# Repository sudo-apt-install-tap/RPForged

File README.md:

## RPFORGED
This is a custom development board based on the RP 2040 Chip. It has 29 GPIO headers. It has 16MiB Flash storage. It is great for those who want minimalism with style.

## Design Decisions

This project was built to be a minimal but flexible RP2040 devboard
that I could understand end-to-end.

- **RP2040** was chosen for its strong ecosystem, PIO support,and availability.
- **USB-C** was used for durability and modern compatibility.
- The board exposes commonly used GPIOs to make it suitable for keyboards, HID projects, and general prototyping.
- The design avoids unnecessary peripherals to keep cost,complexity, and assembly time low.

## What Can This Board Be Used For?

- Custom keyboards and macropads
- RP2040 experimentation and learning
- USB HID projects
- General embedded prototyping

## Images ( RENDERS )

## BOM

PCB + PCBA = $58
Miscellaneous Costs = $2

## Manufacturing Plan

For this project, only **2 boards will be assembled through JLCPCB**
to validate the design and ensure reliability.

Any additional boards will be assembled by hand using a hotplate once I have access to one. This allows me to learn hands-on SMD assembly while keeping costs low and avoiding unnecessary PCBA orders.

## Build Images and Videos

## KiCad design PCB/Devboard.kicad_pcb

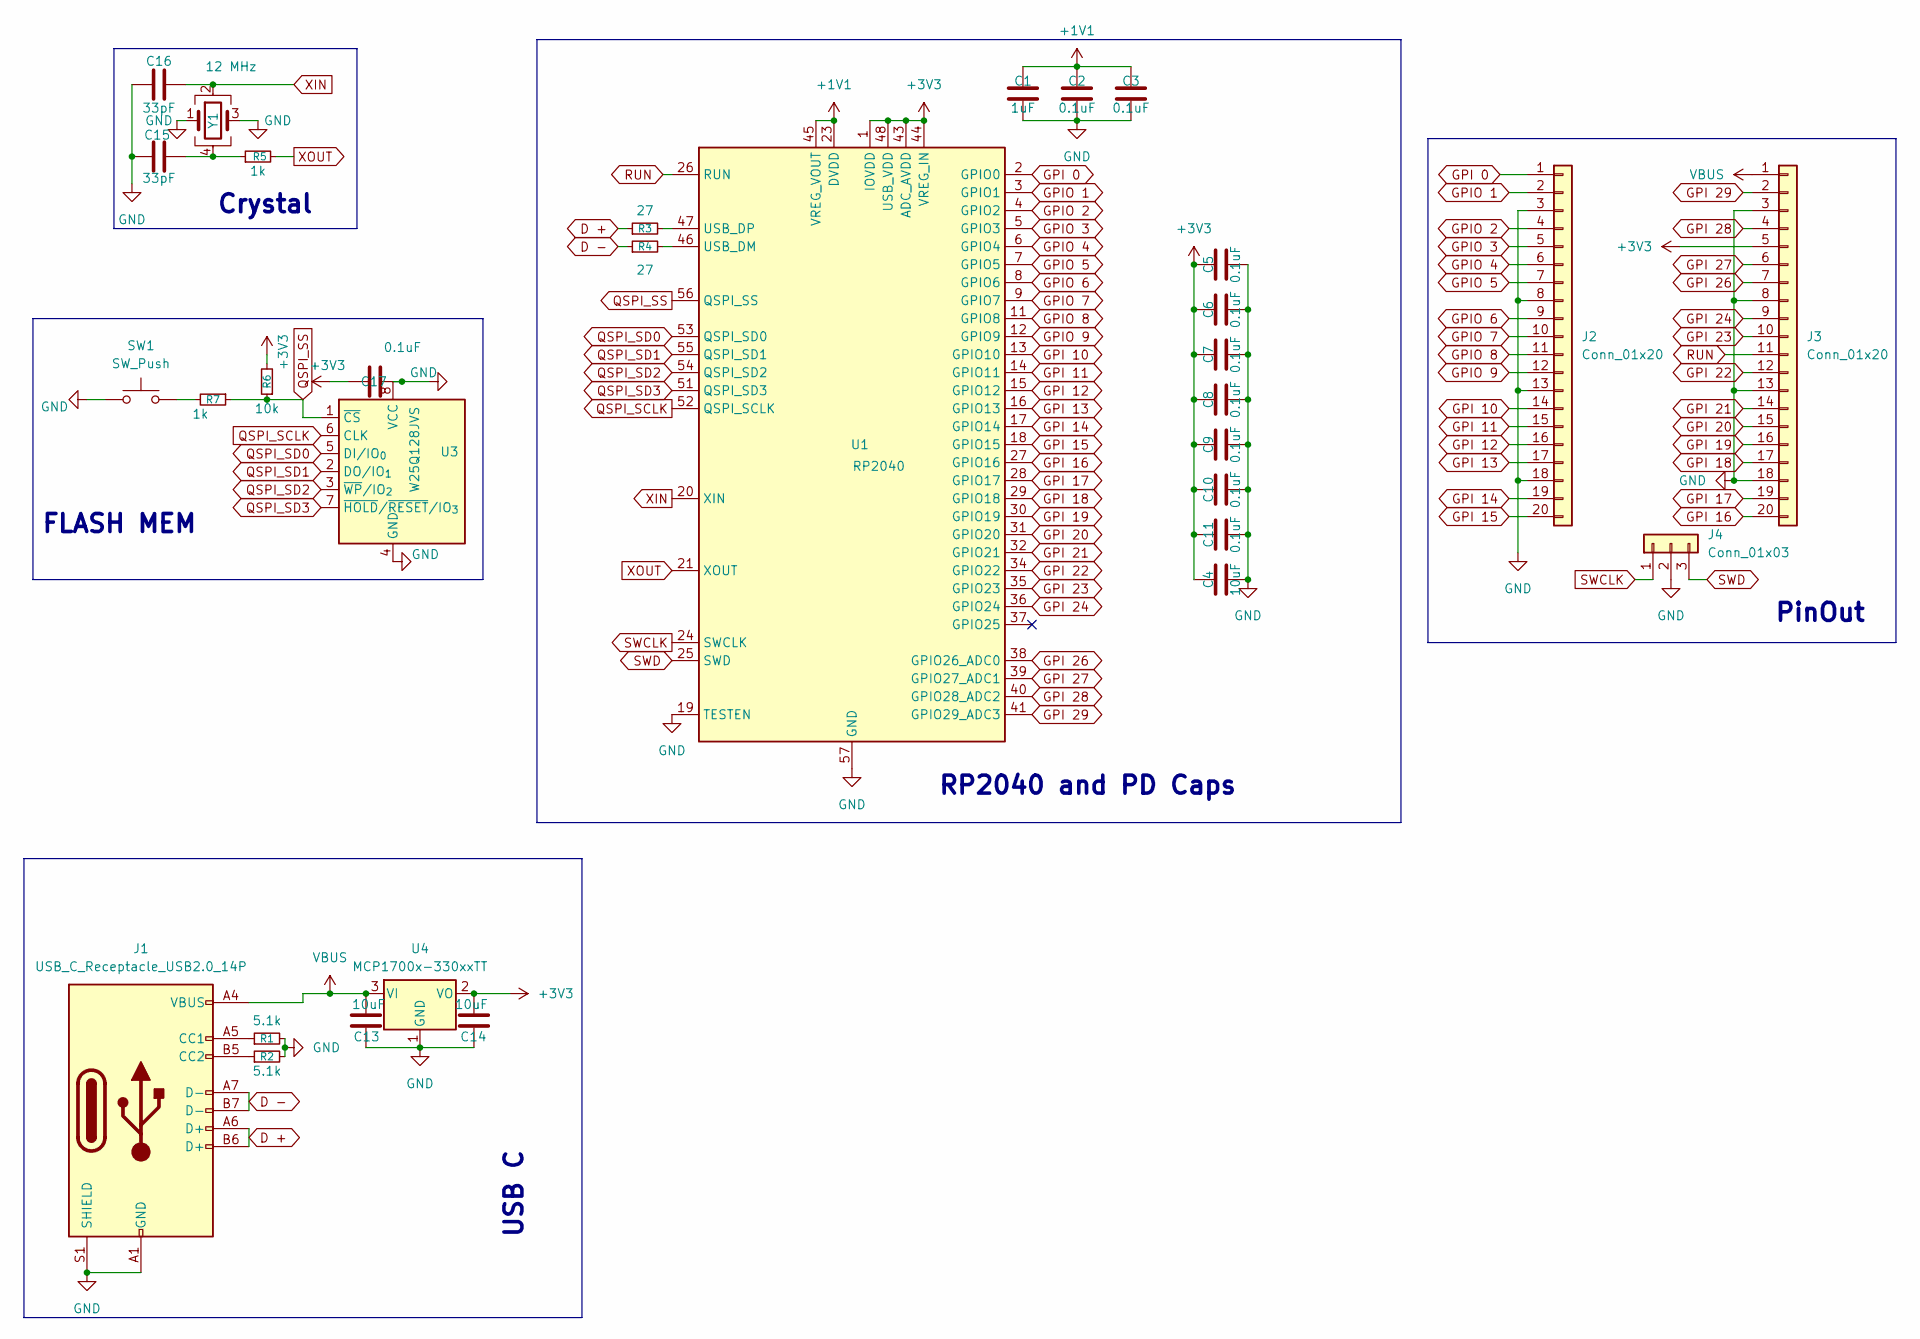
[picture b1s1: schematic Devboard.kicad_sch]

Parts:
C1: 1uF; C_0402_1005Metric
C2, C3, C5, C6, C7, C8, C9, C10, C11, C17: 0.1uF; C_0402_1005Metric
C4: 10uF; C_0402_1005Metric
C13, C14: 10uF; C_0201_0603Metric
C15, C16: 33pF; C_0402_1005Metric
J1: USB_C_Receptacle_USB2.0_14P; USB_C_Receptacle_HRO_TYPE-C-31-M-12
J2, J3: Conn_01x20; PinHeader_1x20_P2.54mm_Vertical
J4: Conn_01x03; PinHeader_1x03_P2.54mm_Vertical
R1, R2: 5.1k; R_0402_1005Metric
R3, R4: 27; R_0402_1005Metric
R5, R7: 1k; R_0402_1005Metric
R6: 10k; R_0402_1005Metric
SW1: SW_Push; SW_Push_SPST_NO_Alps_SKRK
U1: RP2040; QFN-56-1EP_7x7mm_P0.4mm_EP3.2x3.2mm
U3: W25Q128JVS; Winbond_USON-8-1EP_3x2mm_P0.5mm_EP0.2x1.6mm
U4: MCP1700x-330xxTT; SOT-23
Y1: 12 MHz; Crystal_SMD_3225-4Pin_3.2x2.5mm

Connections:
+1V1: C1.1, C2.1, C3.1, U1.23 (DVDD), U1.45 (VREG_VOUT), U1.50 (DVDD)
+3V3: C4.1, C5.1, C6.1, C7.1, C8.1, C9.1, C10.1, C11.1, C14.2, C17.1, J3.5, R6.2, U1.1 (IOVDD), U1.10 (IOVDD), U1.22 (IOVDD), U1.33 (IOVDD), U1.42 (IOVDD), U1.43 (ADC_AVDD), U1.44 (VREG_IN), U1.48 (USB_VDD), U1.49 (IOVDD), U4.2 (VO)
D +: J1.A6 (D+), J1.B6 (D+), R3.1
D -: J1.A7 (D-), J1.B7 (D-), R4.1
GND: C1.2, C2.2, C3.2, C4.2, C5.2, C6.2, C7.2, C8.2, C9.2, C10.2, C11.2, C13.1, C14.1, C15.2, C16.2, C17.2, J1.A1 (GND), J1.A12 (GND), J1.B1 (GND), J1.B12 (GND), J1.S1 (SHIELD), J2.3, J2.8, J2.13, J2.18, J3.3, J3.8, J3.13, J3.18, J4.2, R1.2, R2.2, SW1.1, U1.19 (TESTEN), U1.57 (GND), U3.4 (GND), U3.8 (VCC), U4.1 (GND), Y1.1, Y1.3
GPI 0: J2.1, U1.2 (GPIO0)
GPI 10: J2.14, U1.13 (GPIO10)
GPI 11: J2.15, U1.14 (GPIO11)
GPI 12: J2.16, U1.15 (GPIO12)
GPI 13: J2.17, U1.16 (GPIO13)
GPI 14: J2.19, U1.17 (GPIO14)
GPI 15: J2.20, U1.18 (GPIO15)
GPI 16: J3.20, U1.27 (GPIO16)
GPI 17: J3.19, U1.28 (GPIO17)
GPI 18: J3.17, U1.29 (GPIO18)
GPI 19: J3.16, U1.30 (GPIO19)
GPI 20: J3.15, U1.31 (GPIO20)
GPI 21: J3.14, U1.32 (GPIO21)
GPI 22: J3.12, U1.34 (GPIO22)
GPI 23: J3.10, U1.35 (GPIO23)
GPI 24: J3.9, U1.36 (GPIO24)
GPI 26: J3.7, U1.38 (GPIO26_ADC0)
GPI 27: J3.6, U1.39 (GPIO27_ADC1)
GPI 28: J3.4, U1.40 (GPIO28_ADC2)
GPI 29: J3.2, U1.41 (GPIO29_ADC3)
GPIO 1: J2.2, U1.3 (GPIO1)
GPIO 2: J2.4, U1.4 (GPIO2)
GPIO 3: J2.5, U1.5 (GPIO3)
GPIO 4: J2.6, U1.6 (GPIO4)
GPIO 5: J2.7, U1.7 (GPIO5)
GPIO 6: J2.9, U1.8 (GPIO6)
GPIO 7: J2.10, U1.9 (GPIO7)
GPIO 8: J2.11, U1.11 (GPIO8)
GPIO 9: J2.12, U1.12 (GPIO9)
unnamed: C15.1, R5.1, Y1.4
unnamed: J1.A5 (CC1), R1.1
unnamed: J1.B5 (CC2), R2.1
unnamed: R7.2, SW1.2
unnamed: R4.2, U1.46 (USB_DM)
unnamed: R3.2, U1.47 (USB_DP)
QSPI_SCLK: U1.52 (QSPI_SCLK), U3.6 (CLK)
QSPI_SD0: U1.53 (QSPI_SD0), U3.5 (DI/IO_{0})
QSPI_SD1: U1.55 (QSPI_SD1), U3.2 (DO/IO_{1})
QSPI_SD2: U1.54 (QSPI_SD2), U3.3 (~WP/IO_{2})
QSPI_SD3: U1.51 (QSPI_SD3), U3.7 (~HOLD/~RESET/IO_{3})
QSPI_SS: R6.1, R7.1, U1.56 (QSPI_SS), U3.1 (~CS)
RUN: J3.11, U1.26 (RUN)
SWCLK: J4.1, U1.24 (SWCLK)
SWD: J4.3, U1.25 (SWD)
VBUS: C13.2, J1.A4 (VBUS), J1.A9 (VBUS), J1.B4 (VBUS), J1.B9 (VBUS), J3.1, U4.3 (VI)
XIN: C16.1, U1.20 (XIN), Y1.2
XOUT: R5.2, U1.21 (XOUT)

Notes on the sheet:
USB C
PinOut
FLASH MEM
RP2040 and PD Caps
Crystal

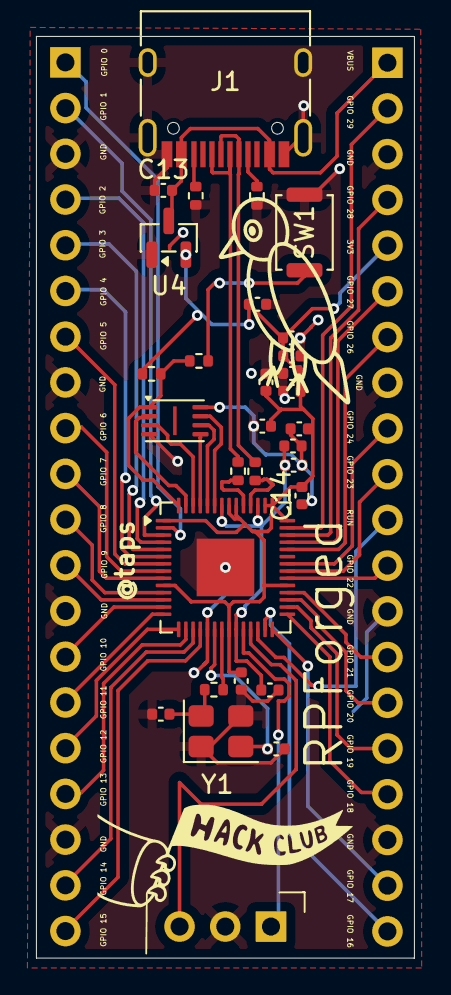
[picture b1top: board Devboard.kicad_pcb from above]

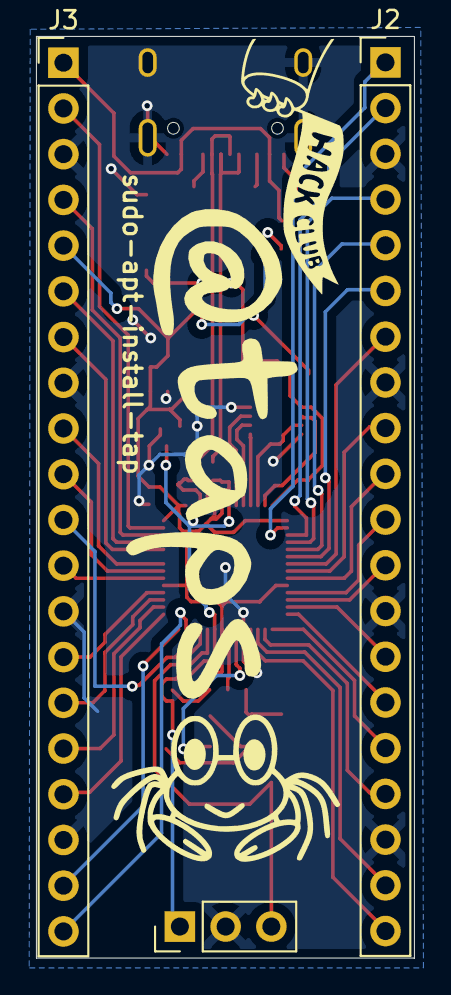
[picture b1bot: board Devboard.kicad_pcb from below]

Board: 2 copper layers, 21.0 x 51.2 mm, 32 parts (3 on the bottom side), 52 nets.

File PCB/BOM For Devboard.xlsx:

Id | Designator | Footprint | Quantity | Comment | Supplier and ref
1 | C9,C5,C7,C11,C3,C10,C8,C6,C2,C17 | C_0402_1005Metric | 10 | 0.1uF
2 | C16,C15 | C_0402_1005Metric | 2 | 33pF
3 | R6 | R_0402_1005Metric | 1 | 10k
4 | R1,R2 | R_0402_1005Metric | 2 | 5.1k
5 | R4,R3 | R_0402_1005Metric | 2 | 27
6 | R7,R5 | R_0402_1005Metric | 2 | 1k
7 | C13,C14 | C_0201_0603Metric | 2 | 10uF
8 | U3 | Winbond_USON-8-1EP_3x2mm_P0.5mm_EP0.2x1.6mm | 1 | W25Q128JVS
9 | J1 | USB_C_Receptacle_HRO_TYPE-C-31-M-12 | 1 | USB_C_Receptacle_USB2.0_14P
10 | C1 | C_0402_1005Metric | 1 | 1uF
11 | SW1 | SW_Push_SPST_NO_Alps_SKRK | 1 | SW_Push
12 | U4 | SOT-23 | 1 | MCP1700x-330xxTT
13 | C4 | C_0402_1005Metric | 1 | 10uF
14 | Y1 | Crystal_SMD_3225-4Pin_3.2x2.5mm | 1 | 12 MHz
15 | U1 | QFN-56-1EP_7x7mm_P0.4mm_EP3.2x3.2mm | 1 | RP2040
16 | J2,J3 | PinHeader_1x20_P2.54mm_Vertical | 2 | Conn_01x20
17 | J4 | PinHeader_1x03_P2.54mm_Vertical | 1 | Conn_01x03

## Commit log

2026-01-06 Added /Images
2026-01-06 Wrote readme.md
2026-01-06 Add RPFORGED section and BOM details to README
2026-01-20 Enhance README with design and usage details
    Added design decisions, use cases, and manufacturing plan sections to provide more context about the RP2040 development board.
2026-01-20 Update BOM cost from $60.99 to $58
2026-01-20 Added images via cli cuz i forgot to do it
2026-01-23 Add images section to README
    Added images section with relevant images to README.
2026-02-09 updated pcb with vias insted of micro vias
2026-03-06 Add build images and videos to README
    Added build images and videos section with embedded content.
2026-03-06 Fix build images and videos section in README
    Updated the build images and videos section with proper iframe and image tags.
2026-03-06 Fix image and video links formatting in README
    Updated image and video links in the README.
2026-03-06 Update README with embedded video and image links
    Replaced video link with an embedded YouTube video and updated image references.
2026-03-31 Update README to include images and YouTube link
    Replaced YouTube iframe with a direct link and added images.
2026-06-01 Add development journal for RPForged RP2040 devboard
    Documented the development process of the RPForged RP2040 devboard, including schematic design, routing, PCB ordering, and troubleshooting.
2026-06-01 Fix formatting and text in JOURNAL.md
    Updated formatting and corrected text in JOURNAL.md.
